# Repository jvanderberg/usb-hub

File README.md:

# usb-hub

A 10-port USB-C bench hub: USB 2.0 High Speed (480 Mbps) on every port, powered from a USB-C PD charger.

| | |
|---|---|
| Downstream | 10x USB-C, USB 2.0 HS, 5 V with a per-port current limit, reverse blocking and ESD clamp |
| Upstream | 1x USB-C (HOST), data; never powers the host |
| Power in | 1x USB-C PD (PWR IN), 9-20 V, up to 100 W; with no charger, runs from the host's VBUS (1.78 A limit) |
| 5 V rail | 5.19 V, about 17 A, synchronous buck |
| Board | 85 x 85 mm, 4 layers, all parts on top, JLCPCB economic assembly |
| No MCU | Hub controllers and PD sink are configured by strap pins |

## Gallery

| | |
|---|---|
|  |  |
| Rear: HOST (upstream) and PWR IN | Front edge, ports 4-7 |
|  |  |
| Top | Bottom (no parts on this side) |

### Copper

| | |
|---|---|
|  |  |
| F.Cu + silkscreen: signals and parts | B.Cu: ground pour with short jumps and the D+/D- row ties |
|  | |
| In2.Cu: the 5 V bus plane that feeds every port switch | In1.Cu (not shown) is a solid ground plane |

## How it works

```
PWR IN (USB-C PD) -> TPS25730 PD sink -> VIN 9-20 V -+-> LM5148 buck --+-> 5V_BUS (In2 plane) -> SY6863 switch x10 -> port VBUS
                                                     '-> TPS54202 buck -> 3V3 for the hub ICs
HOST VBUS -> TPS259470 eFuse (only while the buck is off) -------------'
5V_BUS -> SS34 -> VIN   (host mode: keeps the 3V3 buck running)

HOST -> USB2517 (hub A, 7 ports) -> ports 1-6
                                 '-> USB2514B (hub B, 4 ports) -> ports 7-10
```

- **Power.** The TPS25730 is strap-configured (no firmware) to take a PD contract between 9 and 20 V, up to 5 A.
  An LM5148 buck with external MOSFETs turns that into a 5.19 V bus, set high so a port still sees at least 4.75 V
  at 3 A. A small TPS54202 buck makes 3.3 V for the hub chips.
- **Host-powered mode.** With no charger (or a 5 V-only one) the hub still works from the host: a TPS259470 eFuse
  connects HOST VBUS to the 5 V bus whenever the buck's power-good is low, with a 1.78 A limit, a 25 ms soft start and
  true reverse blocking (the hub never drives the host's VBUS). An SS34 diode feeds the 3.3 V buck from the bus.
  Ports are powered too, within what the host port can supply.
- **Ports.** Every port has its own SY6863 switch: current limit around 3.8 A, reverse-current blocking (an A-to-C
  charger plugged into a port can't backfeed the bus), and the fault output wired to the hub's over-current input.
  Each port advertises 3 A on CC. The total is deliberately oversubscribed: ten ports at 3 A is more than the bus can
  supply, and in bench use it never needs to.
- **Data.** Two hub chips in cascade give ten ports from one upstream link. Every port has a TPD4E05U06 flow-through
  ESD clamp on D+, D-, CC1 and CC2, plus a TVS on VBUS.
- **Ports layout.** 1-3 on the left edge, 4-7 on the front, 8-10 on the right; HOST and PWR IN on the back.

## Status

Rev A: schematic, layout and design review done. DRC 0 errors, 0 unconnected; ERC and schematic/board parity clean.
Not yet fabricated. Needs a vented case: the 5 V converter and hub A run warm (see the review).

## Repository

| Path | What |
|---|---|
| `hw/` | KiCad 10 project: schematic sheets, board, JLCPCB part library (JLCImport) and 3D models |
| `tools/` | The generators: `build.sh` rebuilds `hw/` from them (parts import, schematic, netlist, placement, routing) |
| `docs/requirements.md` | Requirements and architecture |
| `docs/power-design.md`, `docs/hub-design.md`, `docs/port-design.md` | Design notes and calculations for each block |
| `docs/review-2026-11-17.md` | Design review: findings, fixes and the decisions taken |
| `docs/design-values.json` | Every computed value with the parts it depends on |
| `docs/datasheets/` | Datasheets of the parts used and the candidates considered |

The schematic and board are generated by scripts: the source of truth is `tools/`, not hand edits in KiCad.
They are built with [kicad-skills](https://github.com/jvanderberg/kicad-skills) (version pinned in
`kicad-skills.lock`).

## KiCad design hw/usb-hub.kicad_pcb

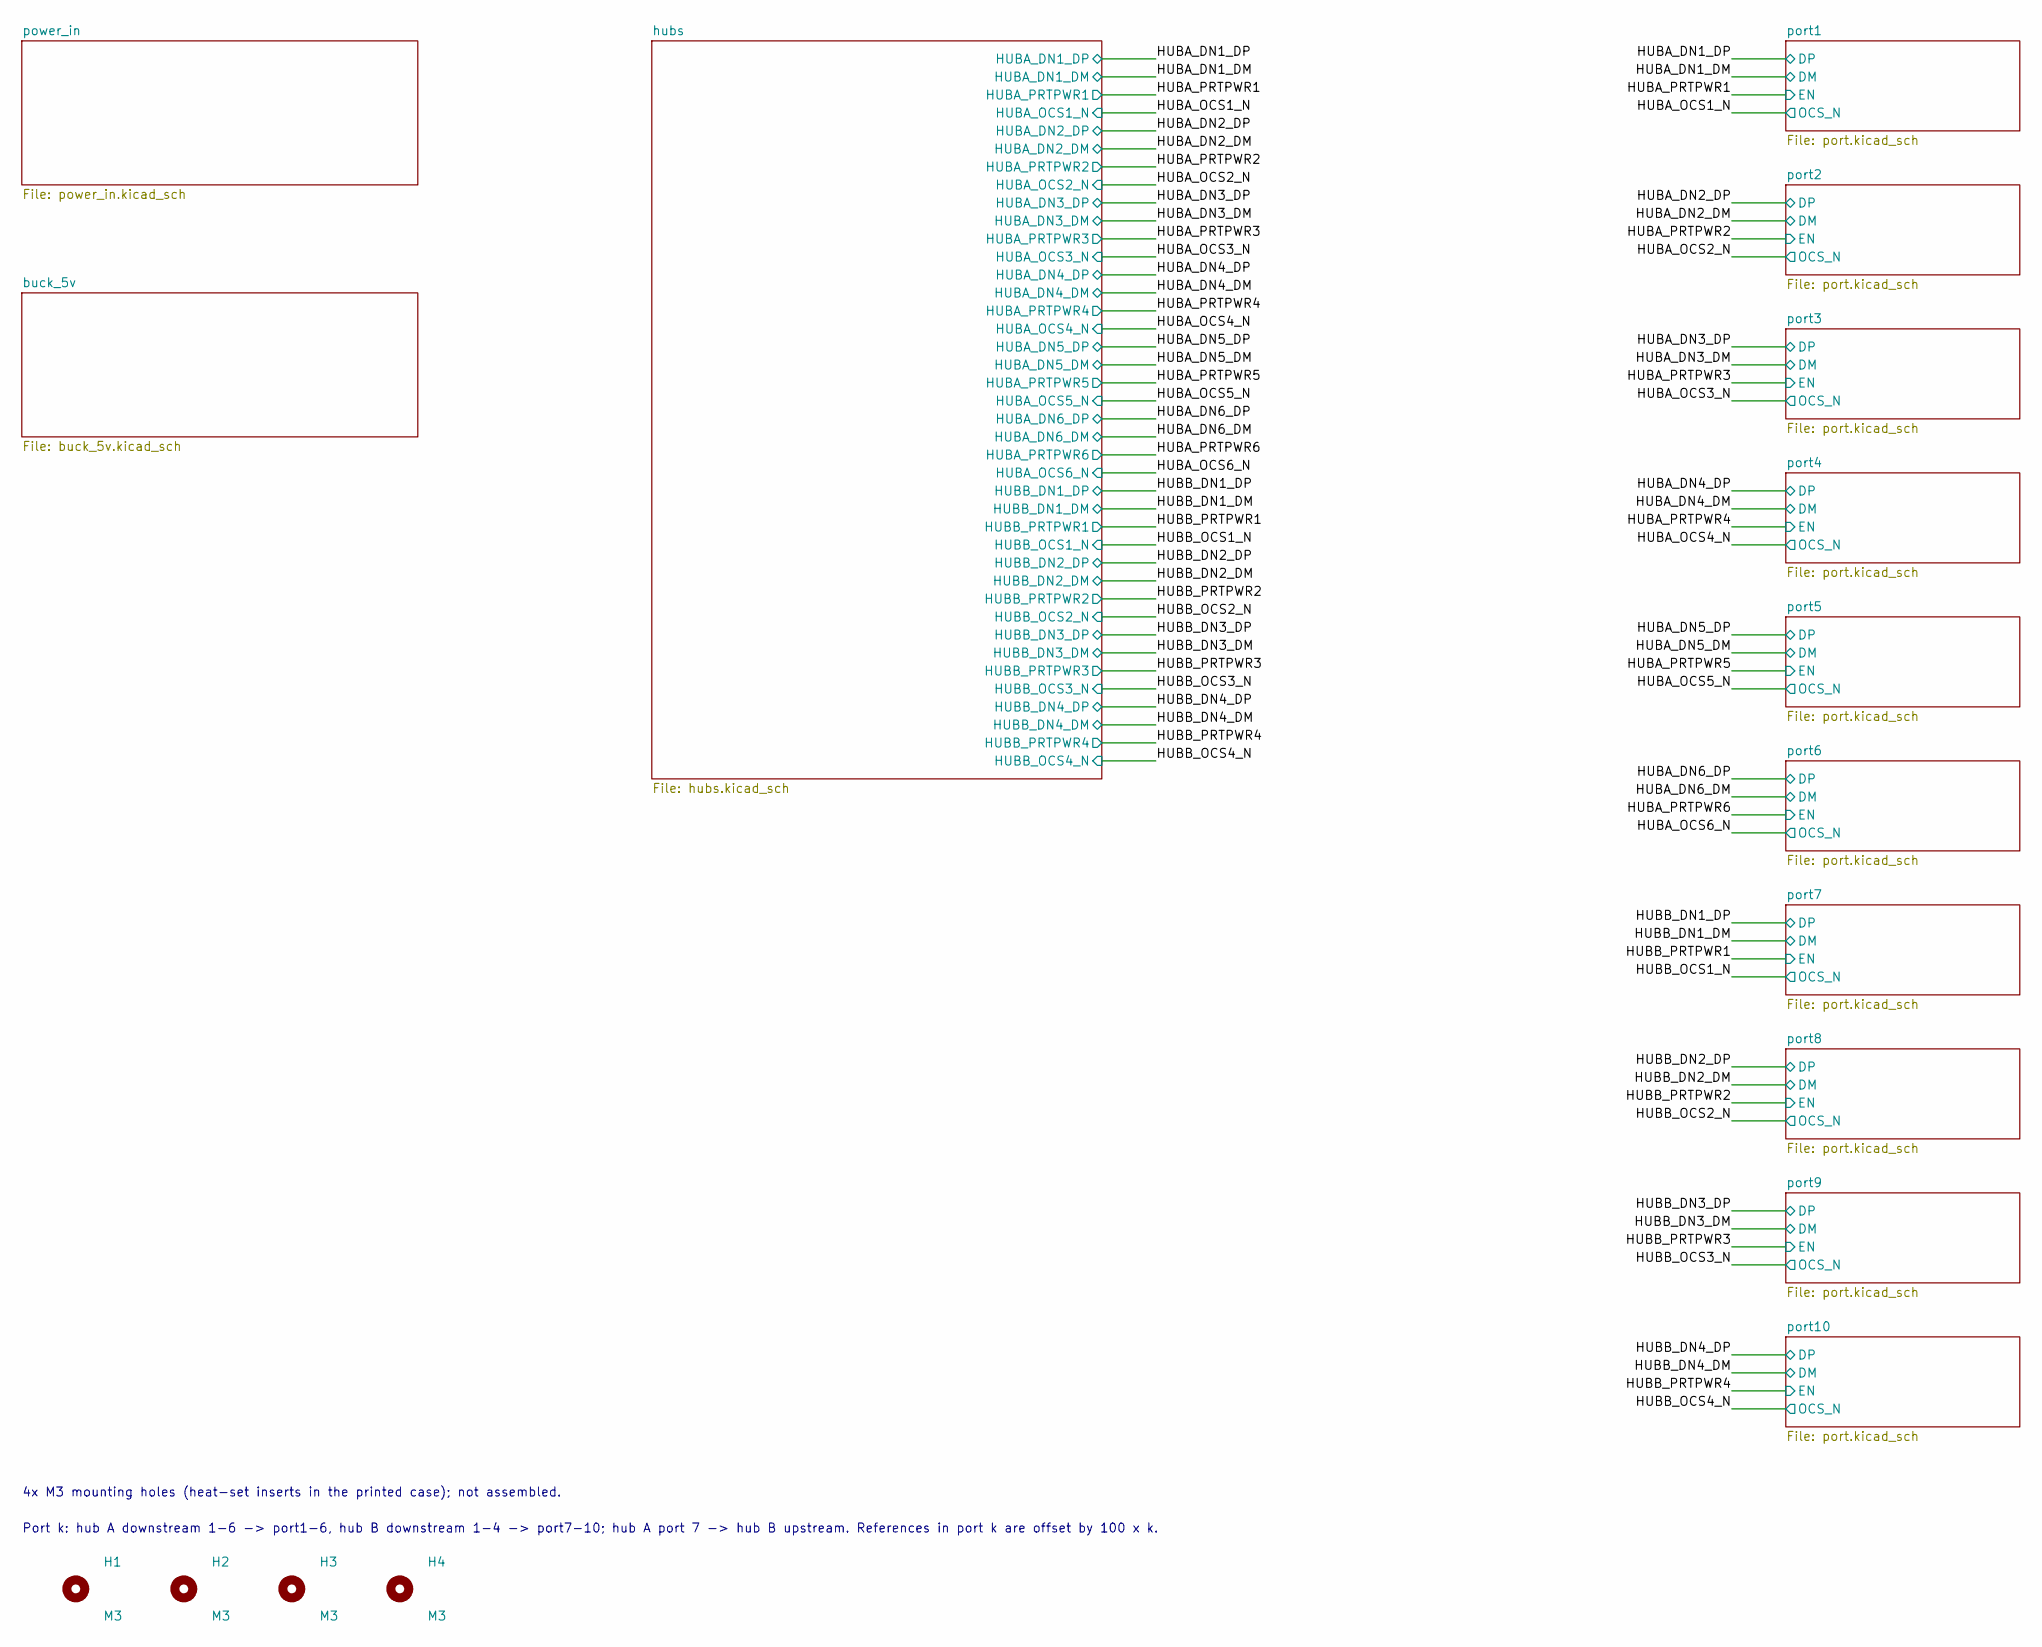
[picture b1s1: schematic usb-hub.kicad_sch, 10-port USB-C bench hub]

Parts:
H1, H2, H3, H4: M3; MountingHole_3.2mm_M3

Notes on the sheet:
4x M3 mounting holes (heat-set inserts in the printed case); not assembled.
Port k: hub A downstream 1-6 -> port1-6, hub B downstream 1-4 -> port7-10; hub A port 7 -> hub B upstream. References in port k are offset by 100 x k.

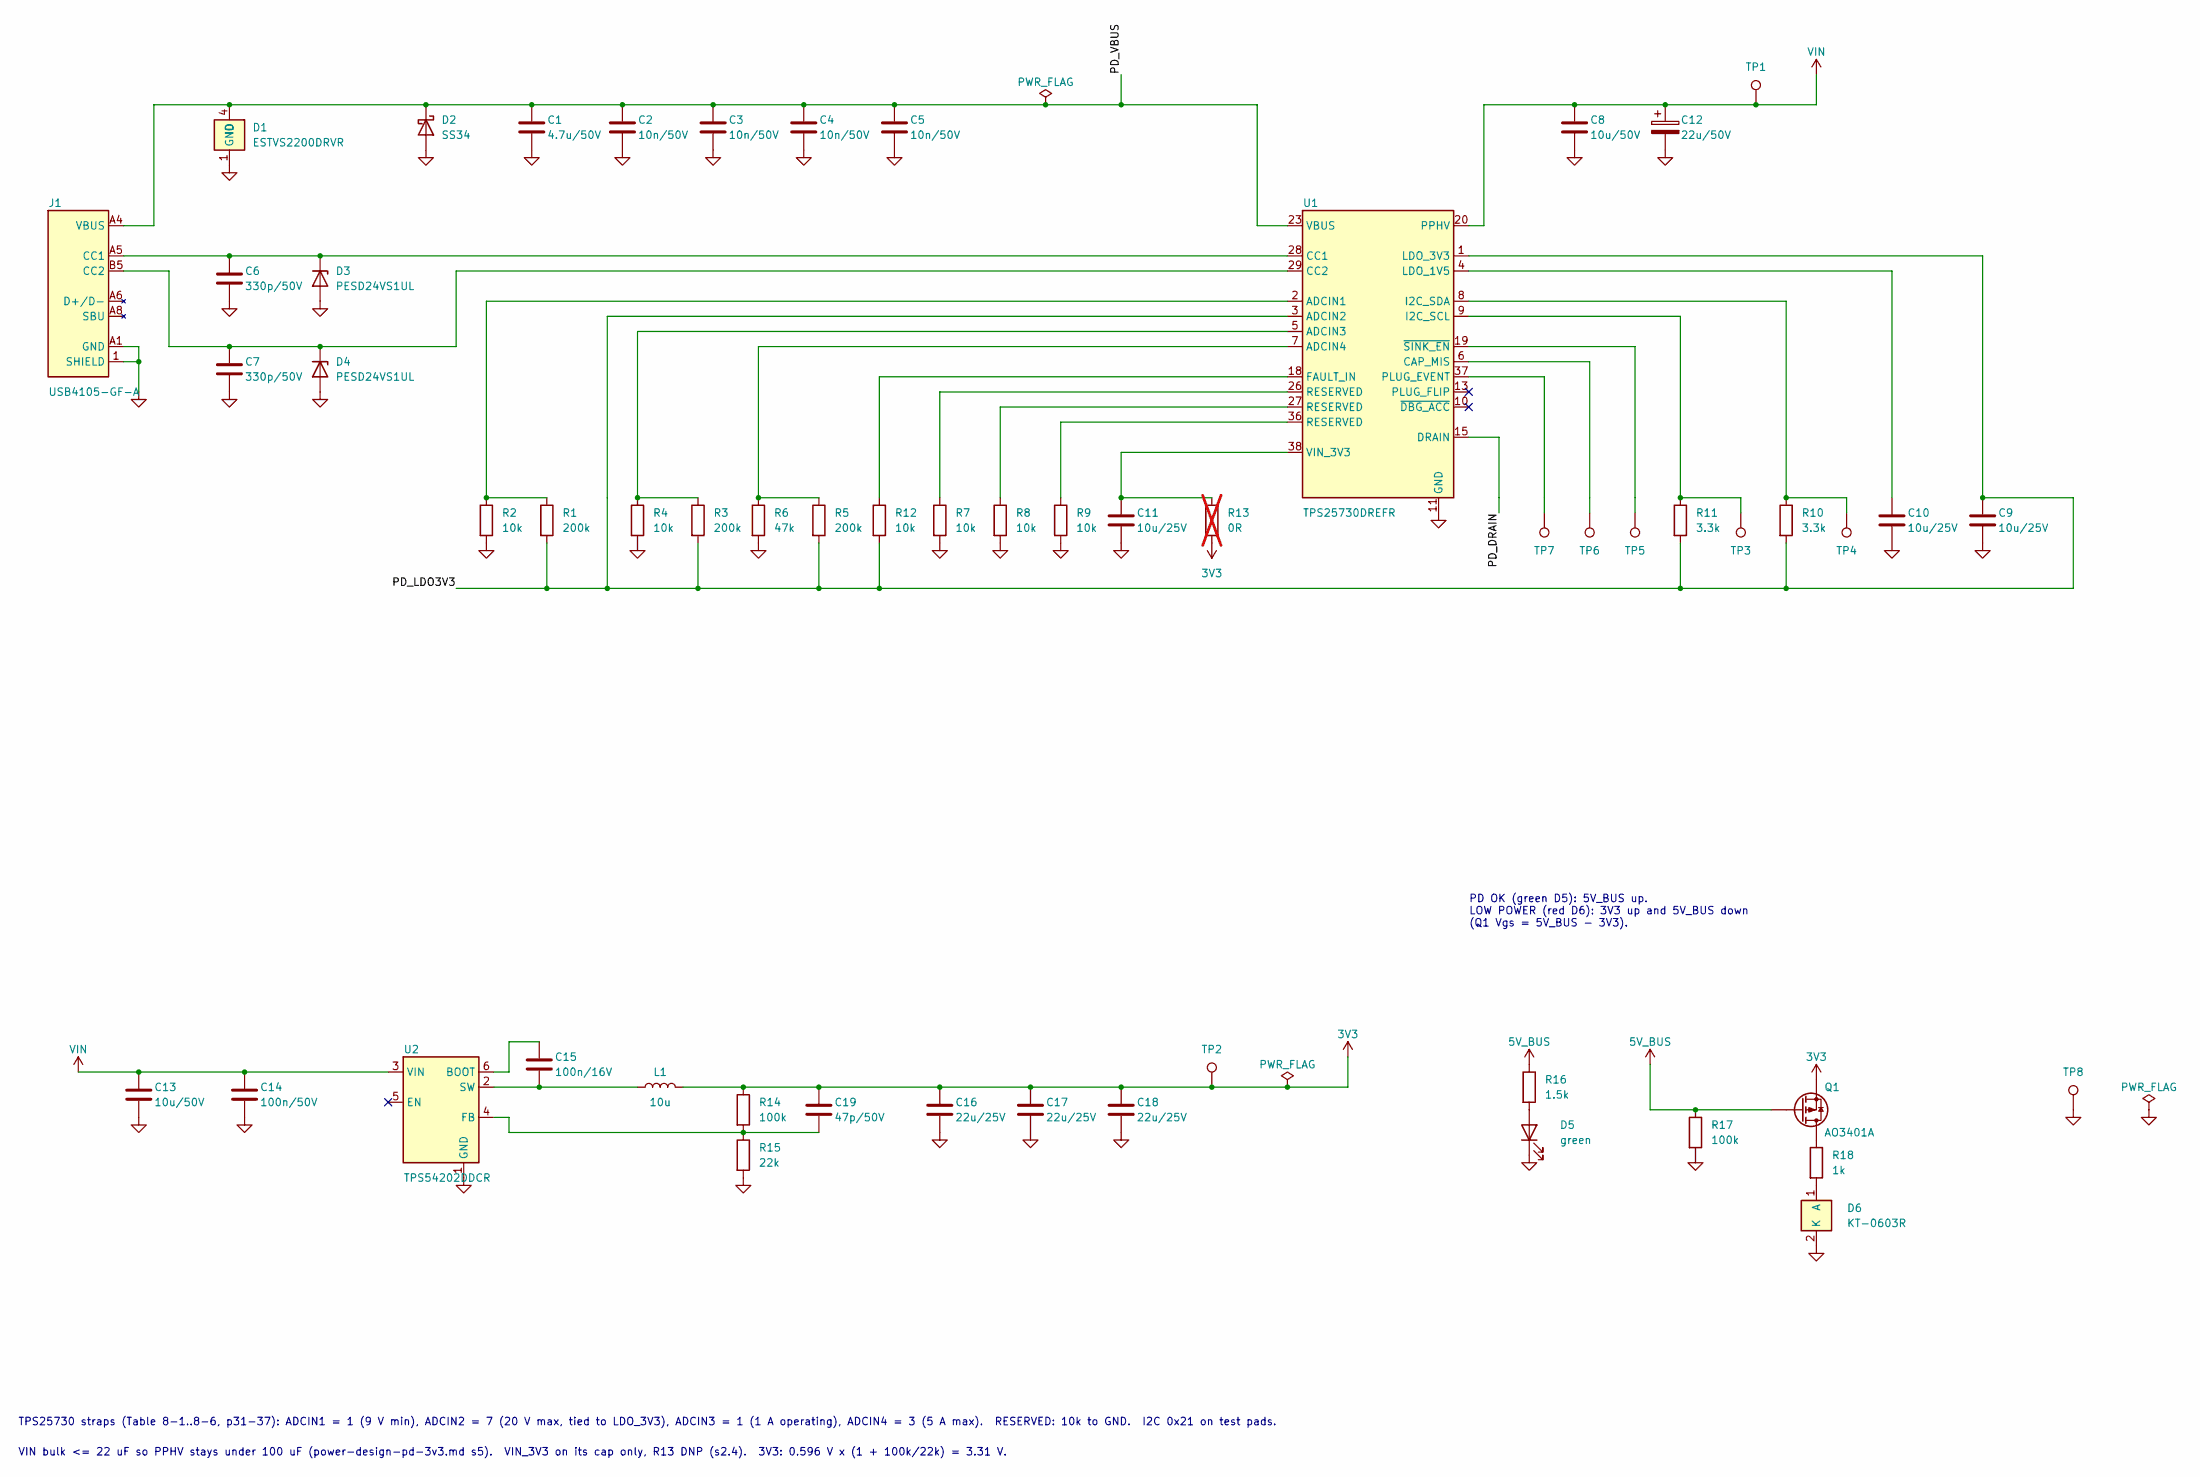
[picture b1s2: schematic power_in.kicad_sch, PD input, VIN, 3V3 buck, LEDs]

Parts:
C1: 4.7u/50V; 1206B475K500NT; Manufacturer Part 1206B475K500NT; LCSC C29823
C2, C3, C4, C5: 10n/50V; CL05B103KB5NNNC; Manufacturer Part CL05B103KB5NNNC; LCSC C15195
C6, C7: 330p/50V; CL10C331JB8NNNC; Manufacturer Part CL10C331JB8NNNC; LCSC C1664
C8, C13: 10u/50V; CL32B106KBJNNNE; Manufacturer Part CL32B106KBJNNNE; LCSC C138687
C9, C10, C11: 10u/25V; CL21A106KAYNNNE; Manufacturer Part CL21A106KAYNNNE; LCSC C15850
C12: 22u/50V; RVT22UF50V67RV0028; Manufacturer Part RVT22UF50V67RV0028; LCSC C2836438
C14: 100n/50V; CL05B104KB54PNC; Manufacturer Part CL05B104KB54PNC; LCSC C307331
C15: 100n/16V; CL05B104KO5NNNC; Manufacturer Part CL05B104KO5NNNC; LCSC C1525
C16, C17, C18: 22u/25V; CL21A226MAQNNNE; Manufacturer Part CL21A226MAQNNNE; LCSC C45783
C19: 47p/50V; 0402CG470J500NT; Manufacturer Part 0402CG470J500NT; LCSC C1567
D1: ESTVS2200DRVR; ESTVS2200DRVR_ThermalVias; Manufacturer Part ESTVS2200DRVR; LCSC C42400188
D2: SS34; SS34_C8678; Manufacturer Part SS34; LCSC C8678
D3, D4: PESD24VS1UL; PESD24VS1UL_315; Manufacturer Part PESD24VS1UL,315; LCSC C477994
D5: green; 0603_Green_509-620mcd; Manufacturer Part KT-0603G; LCSC C12624
D6: KT-0603R; Manufacturer Part KT-0603R; LCSC C2286
J1: USB4105-GF-A; Manufacturer Part USB4105-GF-A; LCSC C3020560
L1: 10u; FXL0630-100-M; Manufacturer Part FXL0630-100-M; LCSC C167223
Q1: AO3401A; Manufacturer Part AO3401A; LCSC C15127
R1, R3, R5: 200k; 0402WGF2003TCE; Manufacturer Part 0402WGF2003TCE; LCSC C25764
R2, R4, R7, R8, R9, R12: 10k; 0402WGF1002TCE; Manufacturer Part 0402WGF1002TCE; LCSC C25744
R6: 47k; 0402WGF4702TCE; Manufacturer Part 0402WGF4702TCE; LCSC C25792
R10, R11: 3.3k; 0402WGF3301TCE; Manufacturer Part 0402WGF3301TCE; LCSC C25890
R13: 0R; 0402WGF0000TCE; Manufacturer Part 0402WGF0000TCE; LCSC C17168; not fitted
R14, R17: 100k; 0402WGF1003TCE; Manufacturer Part 0402WGF1003TCE; LCSC C25741
R15: 22k; 0402WGF2202TCE; Manufacturer Part 0402WGF2202TCE; LCSC C25768
R16: 1.5k; 0402WGF1501TCE; Manufacturer Part 0402WGF1501TCE; LCSC C25867
R18: 1k; 0402WGF1001TCE; Manufacturer Part 0402WGF1001TCE; LCSC C11702
TP1: VIN; TestPoint_Pad_D1.0mm
TP2: 3V3; TestPoint_Pad_D1.0mm
TP3: PD_SCL; TestPoint_Pad_D1.0mm
TP4: PD_SDA; TestPoint_Pad_D1.0mm
TP5: SINK_EN; TestPoint_Pad_D1.0mm
TP6: CAP_MIS; TestPoint_Pad_D1.0mm
TP7: PLUG_EVENT; TestPoint_Pad_D1.0mm
TP8: GND; TestPoint_Pad_D1.0mm
U1: TPS25730DREFR; TPS25730DREFR_ThermalVias; Manufacturer Part TPS25730DREFR; LCSC C22438973
U2: TPS54202DDCR; Manufacturer Part TPS54202DDCR; LCSC C191884

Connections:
3V3: C16.1, C17.1, C18.1, C19.1, L1.2, Q1.2 (S), R13.2, R14.1, TP2.1 (1_1); also elsewhere on the board
5V_BUS: Q1.1 (G), R16.1, R17.1; also elsewhere on the board
/power_in/PD_DRAIN: U1.15 (DRAIN), U1.30 (DRAIN), U1.40 (DRAIN)
/power_in/PD_LDO3V3: C9.1, R1.2, R3.2, R5.2, R10.2, R11.2, R12.2, U1.1 (LDO_3V3), U1.3 (ADCIN2)
/power_in/PD_VBUS: C1.1, C2.1, C3.1, C4.1, C5.1, D1.4 (IO), D1.5 (IO), D1.6 (IO), D2.1 (K), J1.A4 (VBUS), J1.A9 (VBUS), J1.B4 (VBUS), J1.B9 (VBUS), U1.23 (VBUS), U1.24 (VBUS), U1.25 (VBUS), U1.32 (VBUS), U1.33 (VBUS)
GND: C1.2, C2.2, C3.2, C4.2, C5.2, C6.2, C7.2, C8.2, C9.2, C10.2, C11.2, C12.2, C13.2, C14.2, C16.2, C17.2, C18.2, D1.1 (GND), D1.2 (GND), D1.3 (GND), D1.7 (GND), D2.2 (A), D3.2 (A), D4.2 (A), D5.1 (K), D6.2 (K), J1.1 (SHIELD), J1.2 (SHIELD), J1.3 (SHIELD), J1.4 (SHIELD), J1.A1 (GND), J1.A12 (GND), J1.B1 (GND), J1.B12 (GND), R2.2, R4.2, R6.2, R7.2, R8.2, R9.2, R15.2, R17.2, TP8.1 (1_1), U1.11 (GND), U1.12 (GND), U1.14 (GND), U1.16 (GND), U1.17 (GND), U1.31 (GND), U1.34 (GND), U1.35 (GND), U1.39 (GND), U2.1 (GND); also elsewhere on the board
unnamed: C6.1, D3.1 (K), J1.A5 (CC1), U1.28 (CC1)
unnamed: C7.1, D4.1 (K), J1.B5 (CC2), U1.29 (CC2)
unnamed: D5.2 (A), R16.2
unnamed: D6.1 (A), R18.2
unnamed: Q1.3 (D), R18.1
unnamed: R7.1, U1.26 (RESERVED)
unnamed: R8.1, U1.27 (RESERVED)
unnamed: R9.1, U1.36 (RESERVED)
unnamed: R1.1, R2.1, U1.2 (ADCIN1)
unnamed: R3.1, R4.1, U1.5 (ADCIN3)
unnamed: R5.1, R6.1, U1.7 (ADCIN4)
unnamed: TP6.1 (1_1), U1.6 (CAP_MIS)
unnamed: R12.1, U1.18 (FAULT_IN)
unnamed: R11.1, TP3.1 (1_1), U1.9 (I2C_SCL)
unnamed: R10.1, TP4.1 (1_1), U1.8 (I2C_SDA)
unnamed: C10.1, U1.4 (LDO_1V5)
unnamed: TP7.1 (1_1), U1.37 (PLUG_EVENT)
unnamed: C11.1, R13.1, U1.38 (VIN_3V3)
unnamed: TP5.1 (1_1), U1.19 (~SINK_EN)
unnamed: C15.1, U2.6 (BOOT)
unnamed: C19.2, R14.2, R15.1, U2.4 (FB)
unnamed: C15.2, L1.1, U2.2 (SW)
VIN: C8.1, C12.1, C13.1, C14.1, TP1.1 (1_1), U1.20 (PPHV), U1.21 (PPHV), U1.22 (PPHV), U2.3 (VIN); also elsewhere on the board

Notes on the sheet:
PD OK (green D5): 5V_BUS up. LOW POWER (red D6): 3V3 up and 5V_BUS down (Q1 Vgs = 5V_BUS - 3V3).
TPS25730 straps (Table 8-1..8-6, p31-37): ADCIN1 = 1 (9 V min), ADCIN2 = 7 (20 V max, tied to LDO_3V3), ADCIN3 = 1 (1 A operating), ADCIN4 = 3 (5 A max). RESERVED: 10k to GND. I2C 0x21 on test pads.
VIN bulk <= 22 uF so PPHV stays under 100 uF (power-design-pd-3v3.md s5). VIN_3V3 on its cap only, R13 DNP (s2.4). 3V3: 0.596 V x (1 + 100k/22k) = 3.31 V.

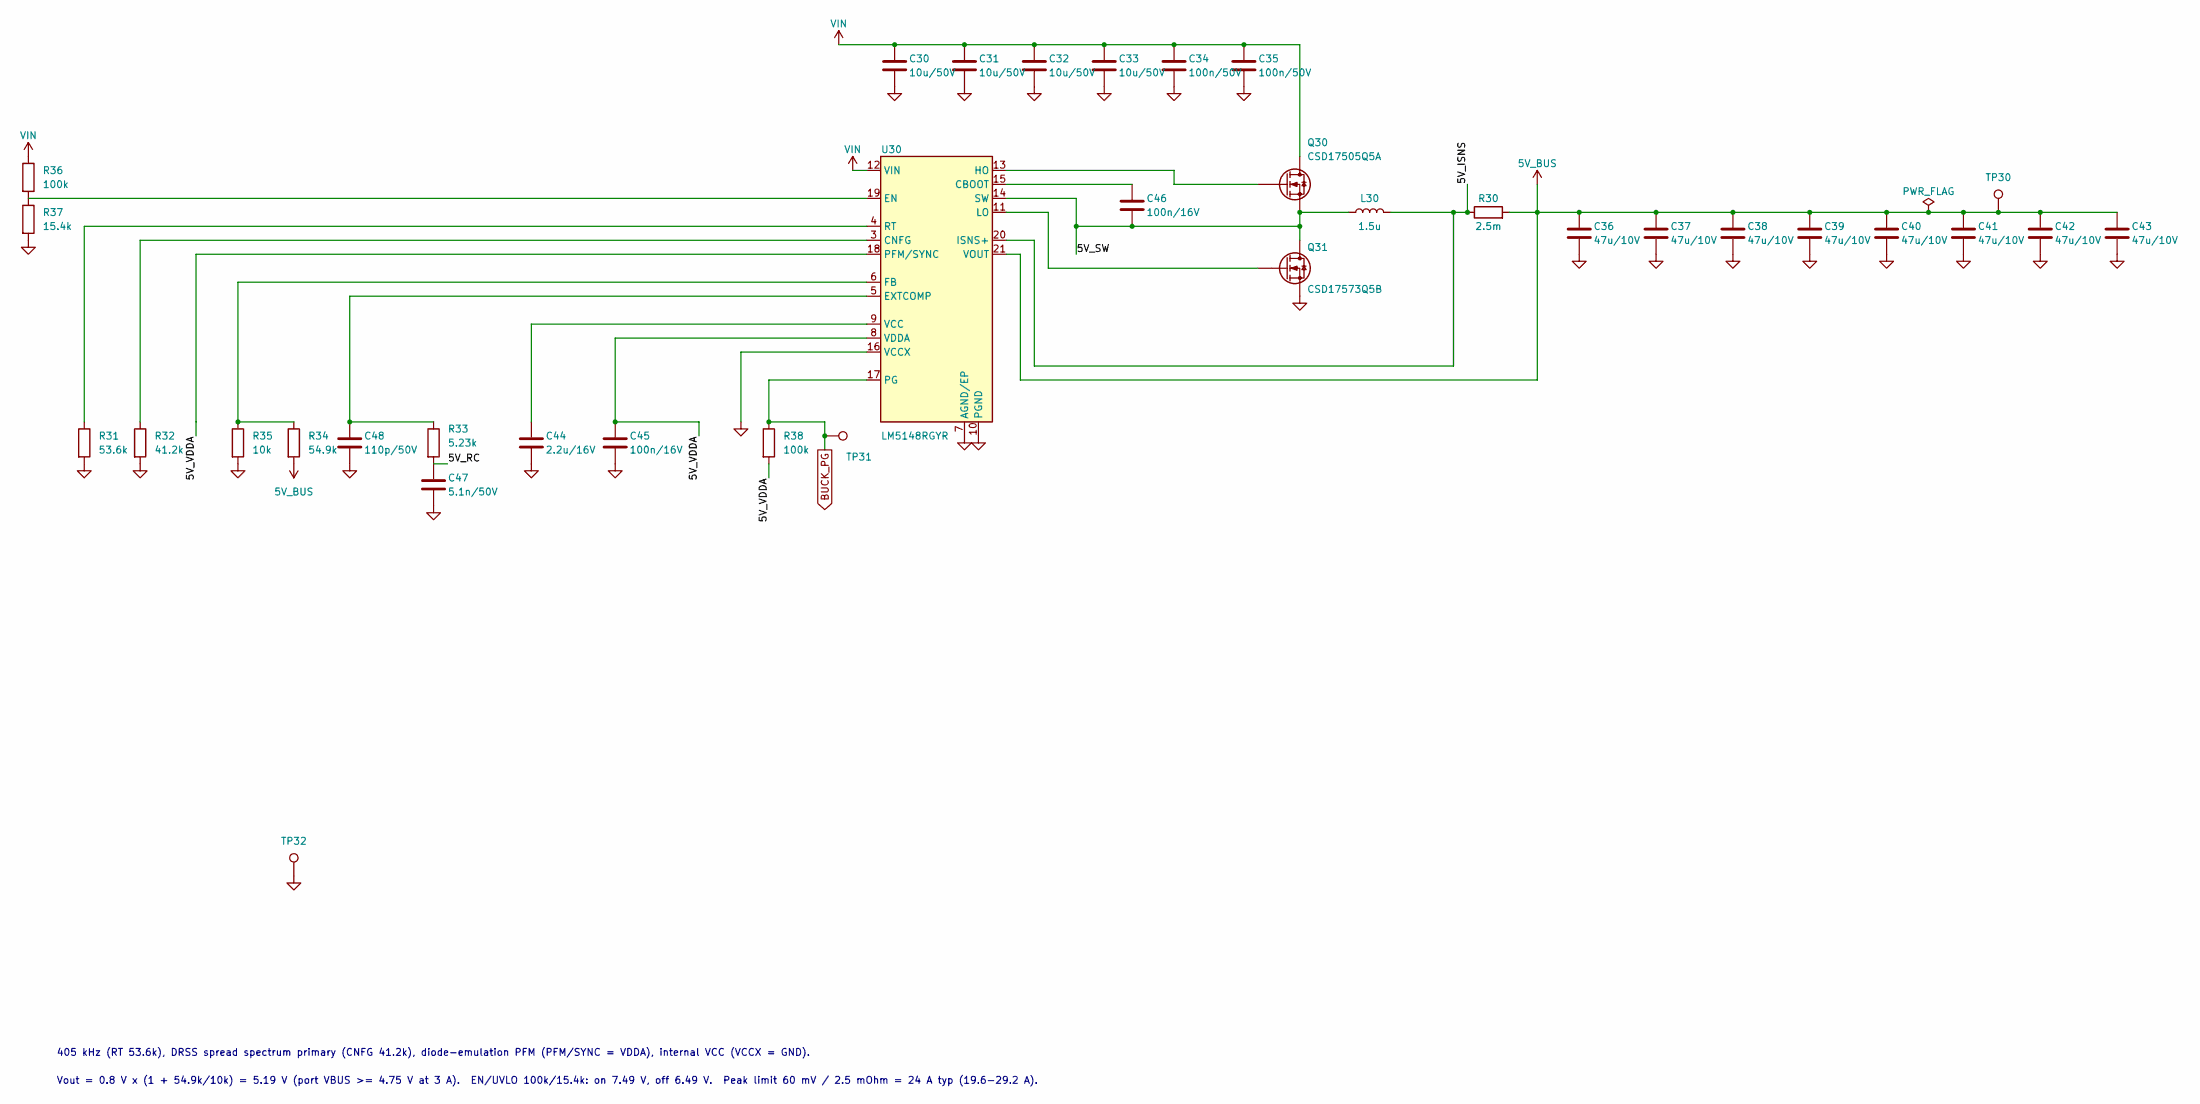
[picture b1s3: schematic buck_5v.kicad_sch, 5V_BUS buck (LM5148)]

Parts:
C30, C31, C32, C33: 10u/50V; CL32B106KBJNNNE; Manufacturer Part CL32B106KBJNNNE; LCSC C138687
C34, C35: 100n/50V; CL05B104KB54PNC; Manufacturer Part CL05B104KB54PNC; LCSC C307331
C36, C37, C38, C39, C40, C41, C42, C43: 47u/10V; CL32A476KPJNNNE; Manufacturer Part CL32A476KPJNNNE; LCSC C525654
C44: 2.2u/16V; CL10A225KO8NNNC; Manufacturer Part CL10A225KO8NNNC; LCSC C23630
C45, C46: 100n/16V; CL05B104KO5NNNC; Manufacturer Part CL05B104KO5NNNC; LCSC C1525
C47: 5.1n/50V; 0402B512K500NT; Manufacturer Part 0402B512K500NT; LCSC C47118429
C48: 110p/50V; CC0402JRNPO9BN111; Manufacturer Part CC0402JRNPO9BN111; LCSC C576704
L30: 1.5u; XAL1010-152MED; Manufacturer Part XAL1010-152MED; LCSC C6753479
Q30: CSD17505Q5A; CSD17505Q5A_ThermalVias; Manufacturer Part CSD17505Q5A; LCSC C553150
Q31: CSD17573Q5B; Manufacturer Part CSD17573Q5B; LCSC C202231
R30: 2.5m; HOJLR2512-3W-2_5MR-1; Manufacturer Part HoJLR2512-3W-2.5mR-1%; LCSC C2904234
R31: 53.6k; 0402WGF5362TCE; Manufacturer Part 0402WGF5362TCE; LCSC C53398
R32: 41.2k; 0402WGF4122TCE; Manufacturer Part 0402WGF4122TCE; LCSC C26978
R33: 5.23k; FRC0402F5231TS; Manufacturer Part FRC0402F5231TS; LCSC C2933105
R34: 54.9k; 0402WGF5492TCE; Manufacturer Part 0402WGF5492TCE; LCSC C11626
R35: 10k; 0402WGF1002TCE; Manufacturer Part 0402WGF1002TCE; LCSC C25744
R36, R38: 100k; 0402WGF1003TCE; Manufacturer Part 0402WGF1003TCE; LCSC C25741
R37: 15.4k; 0402WGF1542TCE; Manufacturer Part 0402WGF1542TCE; LCSC C62740
TP30: 5V_BUS; TestPoint_Pad_D1.0mm
TP31: PG; TestPoint_Pad_D1.0mm
TP32: GND; TestPoint_Pad_D1.0mm
U30: LM5148RGYR; LM5148RGYR_ThermalVias; Manufacturer Part LM5148RGYR; LCSC C7470701

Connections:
5V_BUS: C36.1, C37.1, C38.1, C39.1, C40.1, C41.1, C42.1, C43.1, R30.2, R34.2, TP30.1 (1_1), U30.21 (VOUT); also elsewhere on the board
/buck_5v/5V_ISNS: L30.2, R30.1, U30.20 (ISNS+)
/buck_5v/5V_RC: C47.1, R33.2
/buck_5v/5V_SW: C46.2, L30.1, Q30.1 (S), Q30.2 (S), Q30.3 (S), Q31.5 (D), Q31.6 (D), Q31.7 (D), Q31.8 (D), Q31.9 (D), U30.14 (SW)
/buck_5v/5V_VDDA: C45.1, R38.2, U30.8 (VDDA), U30.18 (PFM/SYNC)
BUCK_PG: R38.1, TP31.1 (1_1), U30.17 (PG); also elsewhere on the board
GND: C30.2, C31.2, C32.2, C33.2, C34.2, C35.2, C36.2, C37.2, C38.2, C39.2, C40.2, C41.2, C42.2, C43.2, C44.2, C45.2, C47.2, C48.2, Q31.1 (S), Q31.2 (S), Q31.3 (S), R31.2, R32.2, R35.2, R37.2, TP32.1 (1_1), U30.1 (AGND/EP), U30.2 (AGND/EP), U30.7 (AGND/EP), U30.10 (PGND), U30.16 (VCCX), U30.22 (AGND/EP), U30.23 (AGND/EP), U30.24 (AGND/EP), U30.25 (AGND/EP); also elsewhere on the board
unnamed: Q30.4 (G), U30.13 (HO)
unnamed: Q31.4 (G), U30.11 (LO)
unnamed: C46.1, U30.15 (CBOOT)
unnamed: R32.1, U30.3 (CNFG)
unnamed: R36.2, R37.1, U30.19 (EN)
unnamed: C48.1, R33.1, U30.5 (EXTCOMP)
unnamed: R34.1, R35.1, U30.6 (FB)
unnamed: R31.1, U30.4 (RT)
unnamed: C44.1, U30.9 (VCC)
VIN: C30.1, C31.1, C32.1, C33.1, C34.1, C35.1, Q30.5 (D), Q30.6 (D), Q30.7 (D), Q30.8 (D), Q30.9 (D), R36.1, U30.12 (VIN); also elsewhere on the board

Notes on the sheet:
405 kHz (RT 53.6k), DRSS spread spectrum primary (CNFG 41.2k), diode-emulation PFM (PFM/SYNC = VDDA), internal VCC (VCCX = GND).
Vout = 0.8 V x (1 + 54.9k/10k) = 5.19 V (port VBUS >= 4.75 V at 3 A). EN/UVLO 100k/15.4k: on 7.49 V, off 6.49 V. Peak limit 60 mV / 2.5 mOhm = 24 A typ (19.6-29.2 A).
